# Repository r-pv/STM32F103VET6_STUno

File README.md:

# STM32F103VET6 STUno

An ST development board based on the STM32F103VET6/STM32F103VE (Clock: 72MHz, Flash: 512Kb, Ram:64Kb) MCU (the LQFP-100 version of the famous Blue Pill) compatible with STM32Duino (Arduino).

Pinout:

## Files and Folders description

- **RBOARD_F103VET6** it's the variant board for the STM32 Arduino Core.
- **rSTM32F103VET6** it's the KiCAD 5.1.2 project.
- **rSTM32F103VET6.schematic.pdf** the schematic.

## Install

**Update:** Since STCore version **1.9.0** most of the F103XXXX boards (including this) are already supported, so there is no need to install anything.

- This requires the [STM32 core for arduino](https://github.com/stm32duino/Arduino_Core_STM32/), the ST original.
- I used this [guide to add the board](https://github.com/stm32duino/wiki/wiki/Add-a-new-variant-(board)), you can check it or continue with my suggestions to install the new board.
- Copy the **"RBOARD_F103VET6"** folder to the Arduino **"variants"** folder, in win7 is located at: **c:\Users\\<USERNAME\>\AppData\Local\Arduino15\packages\STM32\hardware\stm32\1.8.0\variants**
- Edit the **"boards.txt"** file, in win7 is located at a lever up than the "variants" folder, search for the **Generic F1** board line and add the lines to leave it as I show you next:

```
GenF1.menu.pnum.Generic_F103RET6=Generic F103RET6 (Blue Button)
GenF1.menu.pnum.Generic_F103RET6.upload.maximum_size=524288
GenF1.menu.pnum.Generic_F103RET6.upload.maximum_data_size=65536
GenF1.menu.pnum.Generic_F103RET6.build.board=GENERIC_F103RET6
GenF1.menu.pnum.Generic_F103RET6.build.product_line=STM32F103xE
GenF1.menu.pnum.Generic_F103RET6.build.variant=Generic_F103Rx

# Generic STM32F103VET6 STUno
GenF1.menu.pnum.RBOARD_F103VET6=STM32F103VET6 STUno
GenF1.menu.pnum.RBOARD_F103VET6.upload.maximum_size=524288
GenF1.menu.pnum.RBOARD_F103VET6.upload.maximum_data_size=65536
GenF1.menu.pnum.RBOARD_F103VET6.build.board=RBOARD_F103VET6
GenF1.menu.pnum.RBOARD_F103VET6.build.product_line=STM32F103xE
GenF1.menu.pnum.RBOARD_F103VET6.build.variant=RBOARD_F103VET6
```
(add after the _"# Generic STM32F103Rx boards (Blue button)"_ section).

That's all.

So on the arduino IDE, on the **boards** menu pick the option _"Generic STM32F1 series"_ and the **board part number:** suboption pick the _"STM32F103VET6 STUno"_ option.

## The real board

**Front**

**Back**

_*The footprint for the second crystal (Y2) was wrong on this board but it's already corrected on the KiCAD files._

## Running some tests

The **STUno** running the Adafruit ILI9341 library over hardware SPI.

_Video in progress..._

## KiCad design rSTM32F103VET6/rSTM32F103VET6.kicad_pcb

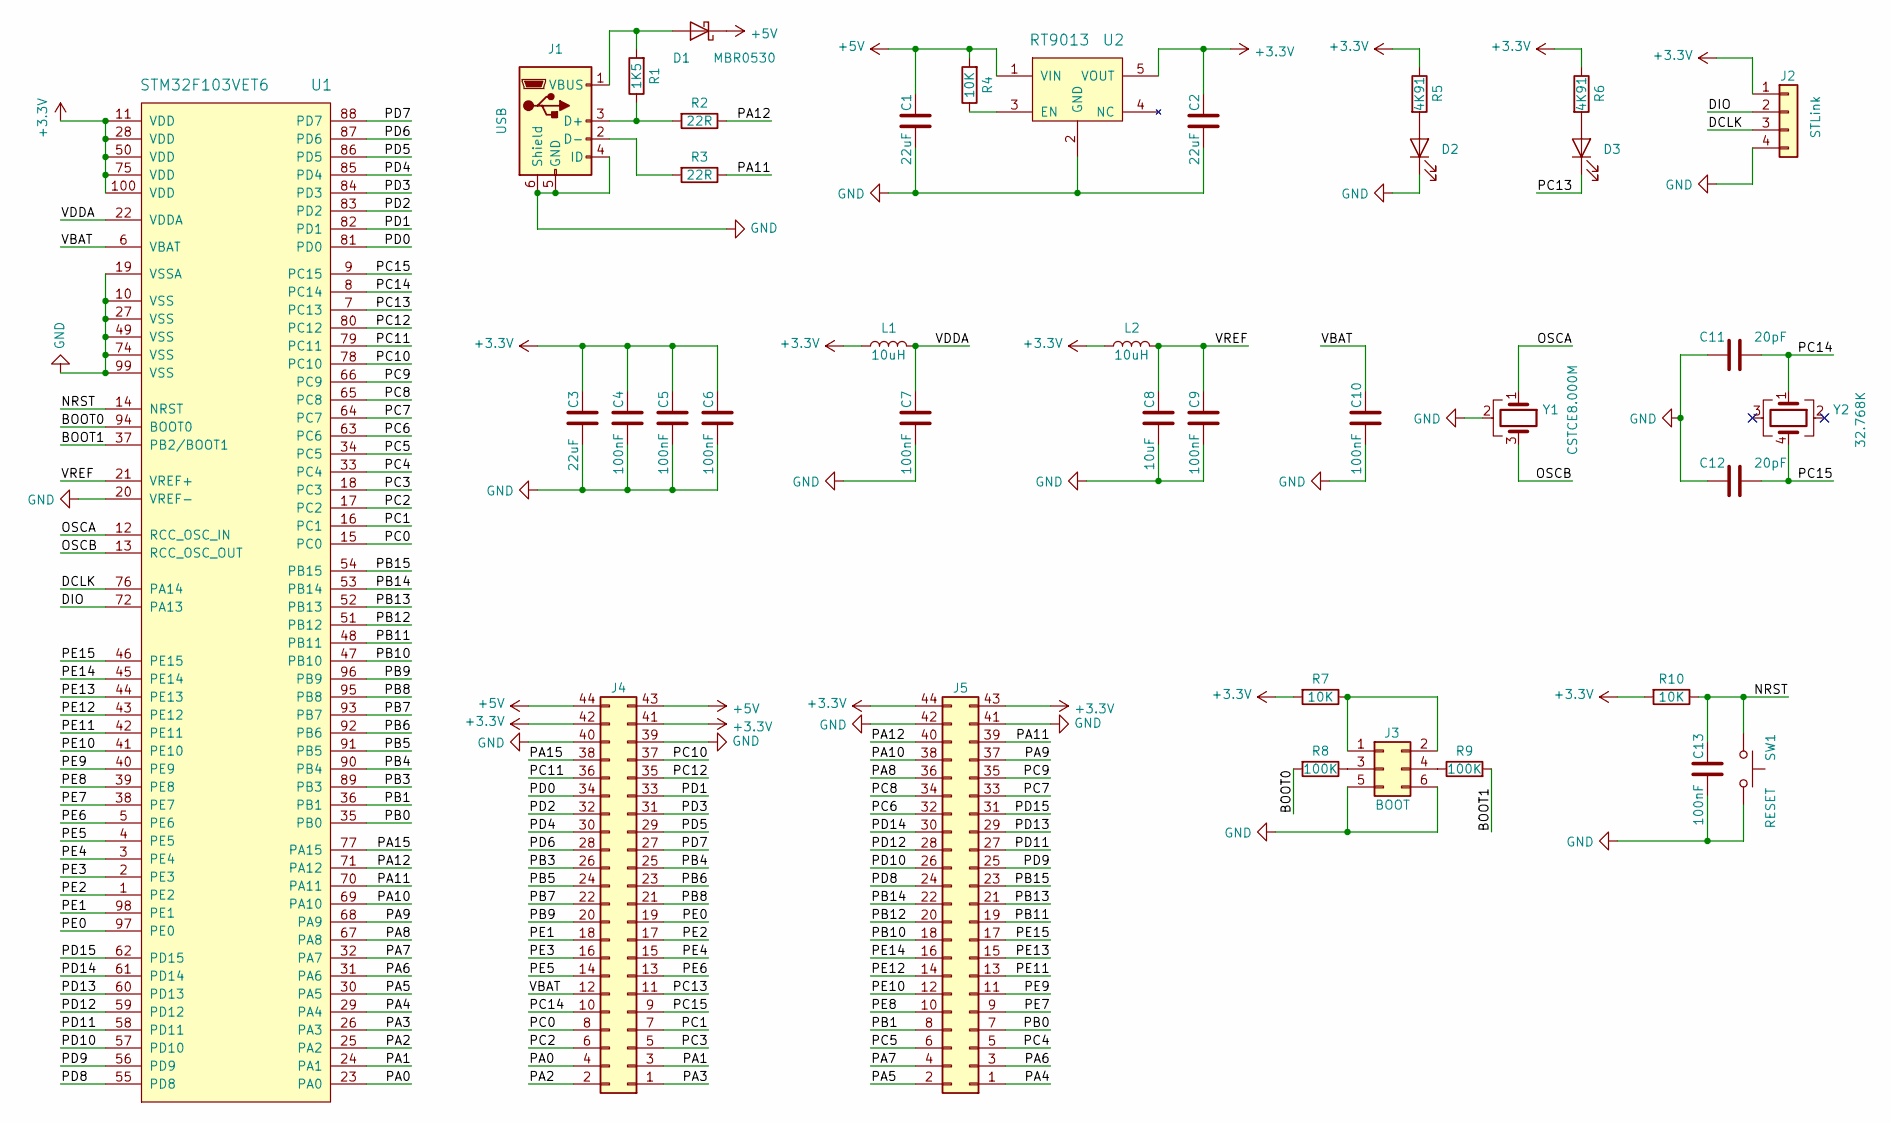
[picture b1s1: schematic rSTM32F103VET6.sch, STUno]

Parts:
C1, C2, C3: 22uF; C_0805
C4, C5, C6, C7, C9, C10, C13: 100nF; C_0805
C8: 10uF; C_0805
C11, C12: 20pF; C_0805
D1: MBR0530; D_SOD-123
D2, D3: LED; LED_0805
J1: USB; USB_Micro-B_Molex_47346-0001
J2: STLink; Pin_Header_Straight_1x04_Pitch2.54mm
J3: BOOT; Pin_Header_Straight_2x03_Pitch2.54mm
J4, J5: Pin_Header_Straight_2x22_Pitch2.54mm
L1, L2: 10uH; L_0805
R1: 1K5; R_0603
R2, R3: 22R; R_0603
R4, R7, R10: 10K; R_0603
R5, R6: 4K91; R_0603
R8, R9: 100K; R_0603
SW1: RESET; Switch_SMD_5.2x6.4_reset
U1: STM32F103VET6; LQFP-100_14x14mm_Pitch0.5mm
U2: RT9013; SOT-23-5
Y1: CSTCE8.000M; Crystal_CSTCE_3pin_3.2x1.3
Y2: 32.768K; Crystal_4pin_SMD_2.5x4.6

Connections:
+3V3: C2.1, C3.1, C4.1, C5.1, C6.1, J2.1, J4.41, J4.42, J5.43, J5.44, L1.1, L2.1, R5.1, R6.1, R7.2, R10.2, U1.11 (VDD), U1.28 (VDD), U1.50 (VDD), U1.75 (VDD), U1.100 (VDD), U2.5 (VOUT)
+5V: C1.1, D1.1 (K), J4.43, J4.44, R4.2, U2.1 (VIN)
/BOOT0: R8.2, U1.94 (BOOT0)
/BOOT1: R9.2, U1.37 (PB2/BOOT1)
/DCLK: J2.3, U1.76 (PA14)
/DIO: J2.2, U1.72 (PA13)
/NRST: C13.1, R10.1, SW1.1, U1.14 (NRST)
/OSCA: U1.12 (RCC_OSC_IN), Y1.1
/OSCB: U1.13 (RCC_OSC_OUT), Y1.3
/PA0: J4.4, U1.23 (PA0)
/PA1: J4.3, U1.24 (PA1)
/PA2: J4.2, U1.25 (PA2)
/PA3: J4.1, U1.26 (PA3)
/PA4: J5.1, U1.29 (PA4)
/PA5: J5.2, U1.30 (PA5)
/PA6: J5.3, U1.31 (PA6)
/PA7: J5.4, U1.32 (PA7)
/PA8: J5.36, U1.67 (PA8)
/PA9: J5.37, U1.68 (PA9)
/PA10: J5.38, U1.69 (PA10)
/PA11: J5.39, R3.1, U1.70 (PA11)
/PA12: J5.40, R2.1, U1.71 (PA12)
/PA15: J4.38, U1.77 (PA15)
/PB0: J5.7, U1.35 (PB0)
/PB1: J5.8, U1.36 (PB1)
/PB3: J4.26, U1.89 (PB3)
/PB4: J4.25, U1.90 (PB4)
/PB5: J4.24, U1.91 (PB5)
/PB6: J4.23, U1.92 (PB6)
/PB7: J4.22, U1.93 (PB7)
/PB8: J4.21, U1.95 (PB8)
/PB9: J4.20, U1.96 (PB9)
/PB10: J5.18, U1.47 (PB10)
/PB11: J5.19, U1.48 (PB11)
/PB12: J5.20, U1.51 (PB12)
/PB13: J5.21, U1.52 (PB13)
/PB14: J5.22, U1.53 (PB14)
/PB15: J5.23, U1.54 (PB15)
/PC0: J4.8, U1.15 (PC0)
/PC1: J4.7, U1.16 (PC1)
/PC2: J4.6, U1.17 (PC2)
/PC3: J4.5, U1.18 (PC3)
/PC4: J5.5, U1.33 (PC4)
/PC5: J5.6, U1.34 (PC5)
/PC6: J5.32, U1.63 (PC6)
/PC7: J5.33, U1.64 (PC7)
/PC8: J5.34, U1.65 (PC8)
/PC9: J5.35, U1.66 (PC9)
/PC10: J4.37, U1.78 (PC10)
/PC11: J4.36, U1.79 (PC11)
/PC12: J4.35, U1.80 (PC12)
/PC13: D3.1 (K), J4.11, U1.7 (PC13)
/PC14: C11.1, J4.10, U1.8 (PC14), Y2.1
/PC15: C12.1, J4.9, U1.9 (PC15), Y2.4
/PD0: J4.34, U1.81 (PD0)
/PD1: J4.33, U1.82 (PD1)
/PD2: J4.32, U1.83 (PD2)
/PD3: J4.31, U1.84 (PD3)
/PD4: J4.30, U1.85 (PD4)
/PD5: J4.29, U1.86 (PD5)
/PD6: J4.28, U1.87 (PD6)
/PD7: J4.27, U1.88 (PD7)
/PD8: J5.24, U1.55 (PD8)
/PD9: J5.25, U1.56 (PD9)
/PD10: J5.26, U1.57 (PD10)
/PD11: J5.27, U1.58 (PD11)
/PD12: J5.28, U1.59 (PD12)
/PD13: J5.29, U1.60 (PD13)
/PD14: J5.30, U1.61 (PD14)
/PD15: J5.31, U1.62 (PD15)
/PE0: J4.19, U1.97 (PE0)
/PE1: J4.18, U1.98 (PE1)
/PE2: J4.17, U1.1 (PE2)
/PE3: J4.16, U1.2 (PE3)
/PE4: J4.15, U1.3 (PE4)
/PE5: J4.14, U1.4 (PE5)
/PE6: J4.13, U1.5 (PE6)
/PE7: J5.9, U1.38 (PE7)
/PE8: J5.10, U1.39 (PE8)
/PE9: J5.11, U1.40 (PE9)
/PE10: J5.12, U1.41 (PE10)
/PE11: J5.13, U1.42 (PE11)
/PE12: J5.14, U1.43 (PE12)
/PE13: J5.15, U1.44 (PE13)
/PE14: J5.16, U1.45 (PE14)
/PE15: J5.17, U1.46 (PE15)
/VBAT: C10.1, J4.12, U1.6 (VBAT)
/VDDA: C7.1, L1.2, U1.22 (VDDA)
/VREF: C8.1, C9.1, L2.2, U1.21 (VREF+)
GND: C1.2, C2.2, C3.2, C4.2, C5.2, C6.2, C7.2, C8.2, C9.2, C10.2, C11.2, C12.2, C13.2, D2.1 (K), J1.4 (ID), J1.5 (GND), J1.6 (Shield), J2.4, J3.5, J3.6, J4.39, J4.40, J5.41, J5.42, SW1.2, U1.10 (VSS), U1.19 (VSSA), U1.20 (VREF-), U1.27 (VSS), U1.49 (VSS), U1.74 (VSS), U1.99 (VSS), U2.2 (GND), Y1.2
unnamed: D1.2 (A), J1.1 (VBUS), R1.2
unnamed: D2.2 (A), R5.2
unnamed: D3.2 (A), R6.2
unnamed: J1.2 (D-), R3.2
unnamed: J1.3 (D+), R1.1, R2.2
unnamed: J3.1, J3.2, R7.1
unnamed: J3.3, R8.1
unnamed: J3.4, R9.1
unnamed: R4.1, U2.3 (EN)

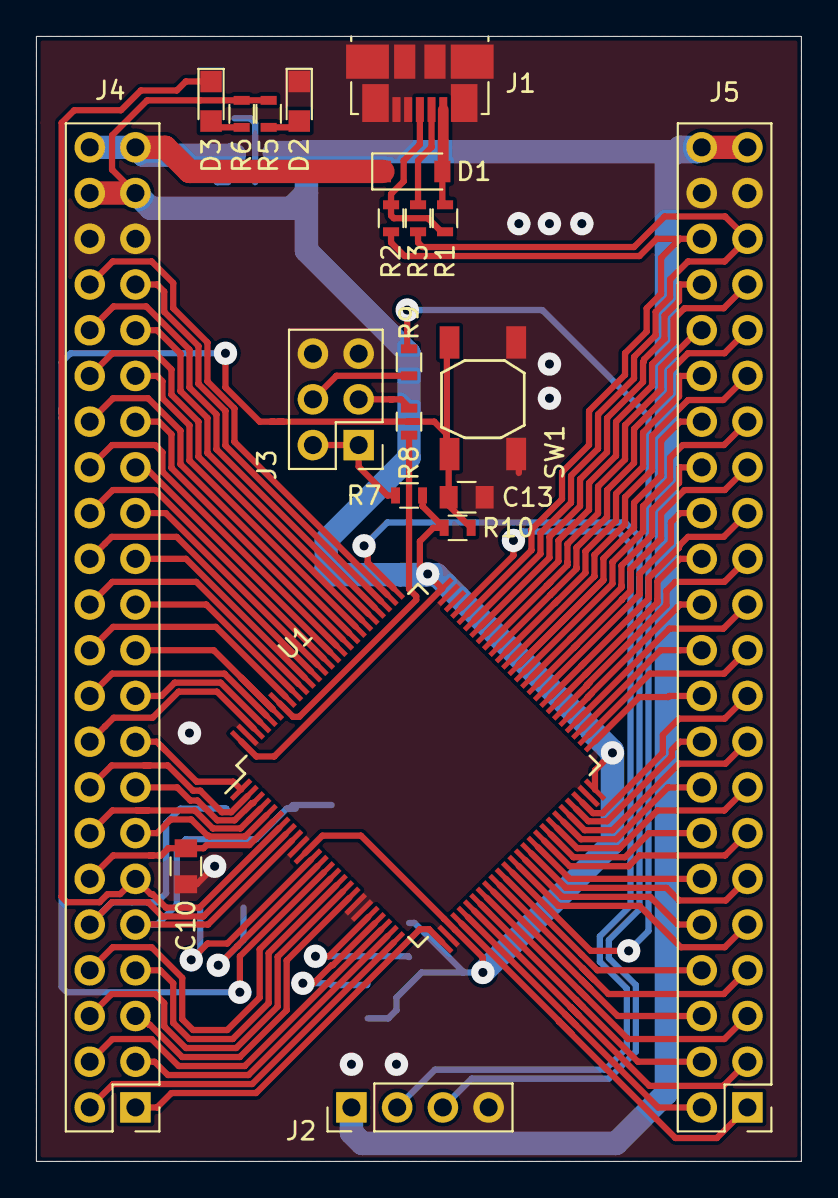
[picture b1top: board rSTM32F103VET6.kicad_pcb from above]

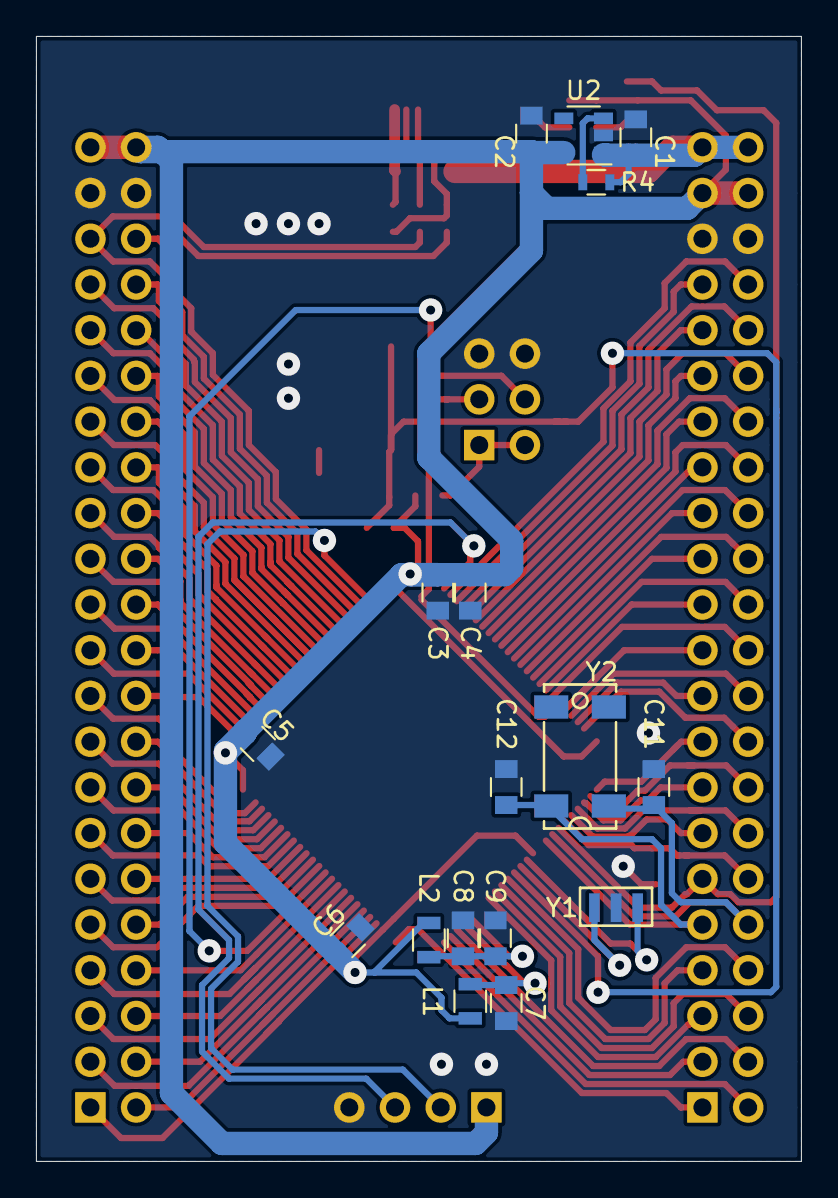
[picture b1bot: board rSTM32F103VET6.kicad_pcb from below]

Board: 2 copper layers, 42.5 x 62.5 mm, 38 parts (17 on the bottom side), 99 nets.

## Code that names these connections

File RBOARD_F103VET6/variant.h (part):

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 *----------------------------------------------------------------------------*/
// USB connector on the top, MCU side
// Left.Side
#define PA15  0
#define PC10  1
#define PC11  2
#define PC12  3
#define PD0   4
#define PD1   5
#define PD2   6
#define PD3   7
#define PD4   8
#define PD5   9
#define PD6   10
#define PD7   11
#define PB3   12
#define PB4   13
#define PB5   14
#define PB6   15
#define PB7   16
#define PB8   17
#define PB9   18
#define PE0   19
#define PE1   20
#define PE2   21
#define PE3   22
#define PE4   23
#define PE5   24
#define PE6   25
/*				 VBAT */
#define PC13  26
#define PC14  27
#define PC15  28
#define PC0   29
#define PC1   30
#define PC2   31
#define PC3   32
#define PA0   33
#define PA1   34
#define PA2   35
#define PA3   36
// Bottom.side
#define PA13  37 //D10   - SWDIO
#define PA14  38 //D11   - SWCLK
// Right.side
#define PA4   39
#define PA5   40
#define PA6   41
#define PA7   42
#define PC4   43
#define PC5   44
#define PB0   45
#define PB1   46
#define PE7   47
#define PE8   48
#define PE9   49
#define PE10  50
#define PE11  51
#define PE12  52
#define PE13  53
#define PE14  54
#define PE15  55
#define PB10  56
#define PB11  57
#define PB12  58
#define PB13  59
#define PB14  60
#define PB15  61
#define PD8   62
#define PD9   63
#define PD10  64
#define PD11  65
#define PD12  66
#define PD13  67
#define PD14  68
#define PD15  69
#define PC6   70
#define PC7   71
#define PC8   72
#define PC9   73
#define PA8   74
#define PA9   75
#define PA10  76
#define PA11  77
#define PA12  78

// Define pin names to match digital pin number --> Dx
// It could be used with preprocessor tests (e.g. #if PXn == 3)
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// !!! // x is PXn (y)
// !!! Ex:
// !!! ...
// !!! #define PA4  20 // A14
// !!! #define PB4  21
// !!! #define PB5  22
// !!! #define PB3  23
// !!! // 24 is PA4 (20)
// !!! // 25 is PB4 (21)
// !!! #define PA2  26 // A15
// !!! ...
//#define PXn x

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//#define PWM_MAX_DUTY_CYCLE      255

// On-board LED pin number
#define LED_BUILTIN             PC13
#define LED_GREEN               LED_BUILTIN

// On-board user button
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// Could be redefined here if differs from the default one
// SPI Definitions
// SPI Definitions
#define PIN_SPI_SS              PA4
#define PIN_SPI_MOSI            PA7
#define PIN_SPI_MISO            PA6
#define PIN_SPI_SCK             PA5

// I2C Definitions
#define PIN_WIRE_SDA            PB7 // Default for Arduino connector compatibility
#define PIN_WIRE_SCL            PB6  // Default for Arduino connector compatibility

// Timer Definitions
// Do not use timer used by PWM pins when possible. See PinMap_PWM.
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#define SERIAL_UART_INSTANCE    1
// Default pin used for 'Serial' instance
// Mandatory for Firmata
#define PIN_SERIAL_RX           PA10
#define PIN_SERIAL_TX           PA9

// UART Definitions
// Define here Serial instance number to map on Serial generic name
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
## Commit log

2019-09-01 KiCAD project.
2019-09-04 KiCAD Project.
    Footprint fix.
2019-09-04 Pinout.
2019-09-05 isn't required.
2019-09-05 updates variant.
2019-09-12 small fix.
2019-10-25 Pinout updated: added ADC and PWM pins.
2019-10-25 Fixed a bug with the analogs.
    Fixed a mistake I made.
2020-02-27 Install info updated.
2020-05-19 info up to 1.9.0 Core.

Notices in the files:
RBOARD_F103VET6/variant.h:
Copyright (c) 2017, STMicroelectronics
All rights reserved.
